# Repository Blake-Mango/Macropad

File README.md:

# Hyperion MacroPad
A macro pad built for multi platform use with a screen to show mode changes and display graphics. I’m going to try and make it wireless as well.

# PCB Assembly & Firmware

## Materials
You will need **all components listed in the Bill of Materials (BOM)** to assemble this board. + the 3d printed case.(currrently pretty bad) 

### Heres what the PCB should look like

---

## Assembly Steps

1. **Solder the KB2040**  
   Begin by attaching the KB2040 to the PCB.

2. **Solder all diodes**  
   Ensure *all diodes are facing the same direction* according to the silkscreen/polarity marking.

3. **Solder all switches**  
   Install and solder all mechanical switches.

4. **Solder remaining components**  
   Add the rest of the components from the BOM (connectors, headers, LEDs, etc.).

---

## Firmware

Firmware is provided in the **`hyperion`** file.  
It is a simple custom program created with help from ChatGPT.

To install:
1. Put the KB2040 into **UF2 bootloader mode**.  
2. Drag and drop the `hyperion` firmware file onto the device.  
3. The board will reboot automatically.

I have made a case but it is very bad i will be making a new case in a day or two just need to look around and see what looks good

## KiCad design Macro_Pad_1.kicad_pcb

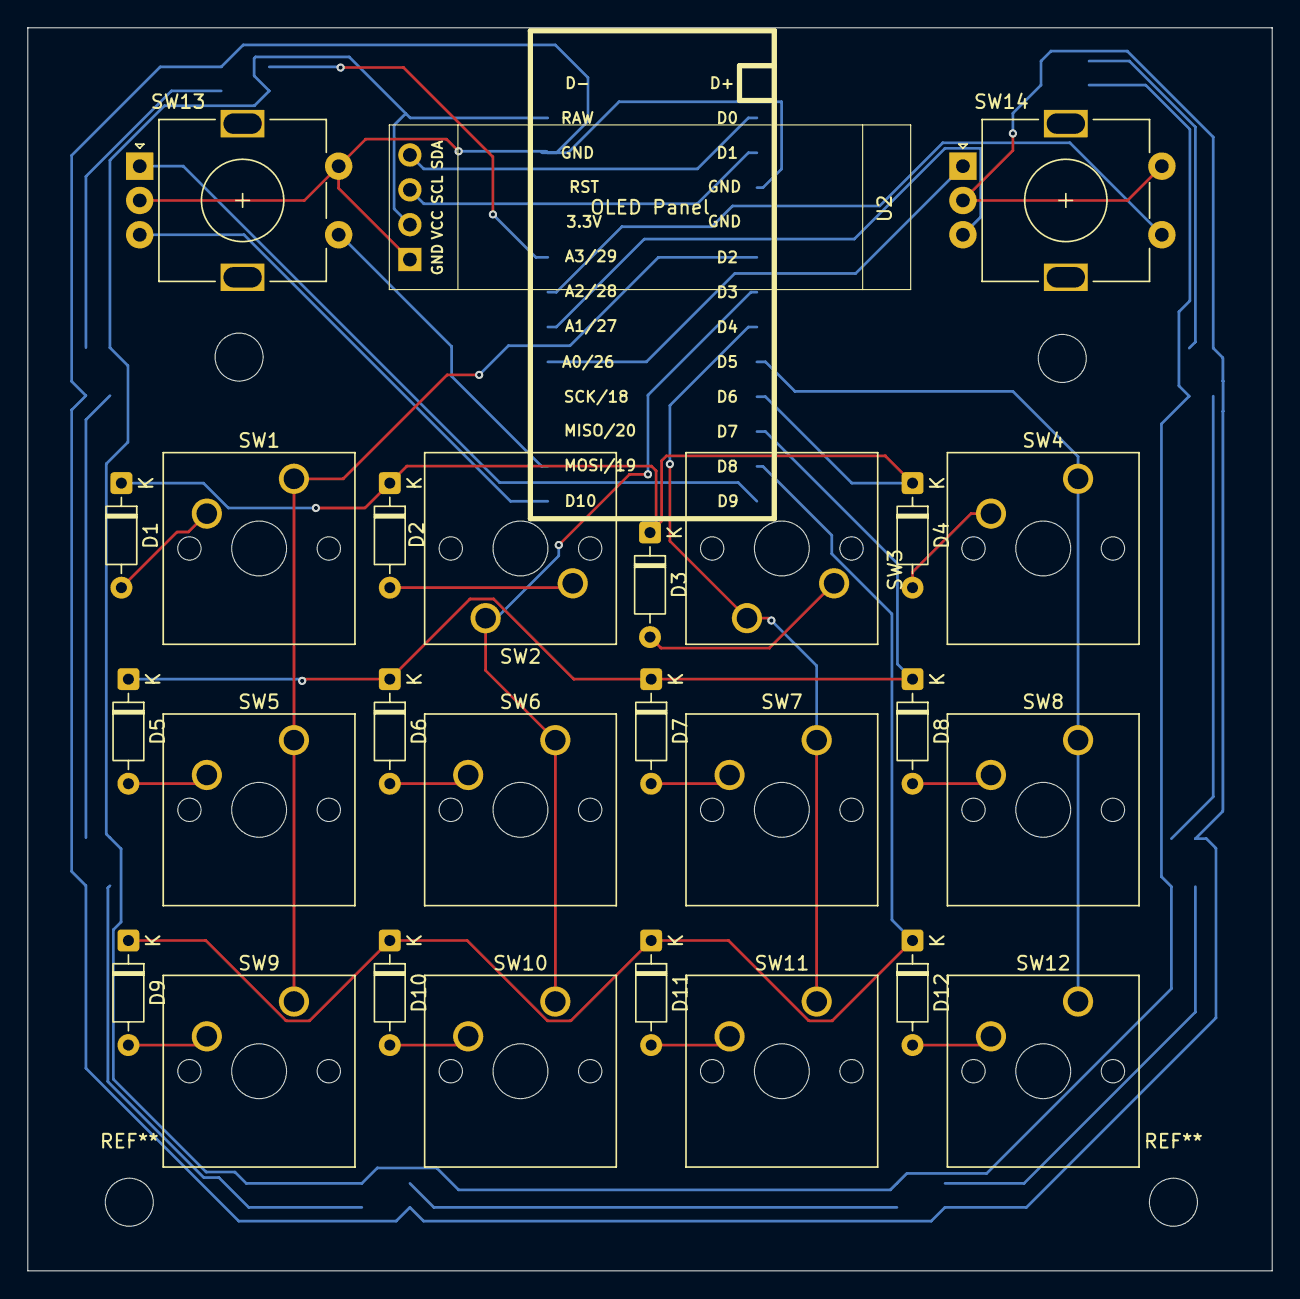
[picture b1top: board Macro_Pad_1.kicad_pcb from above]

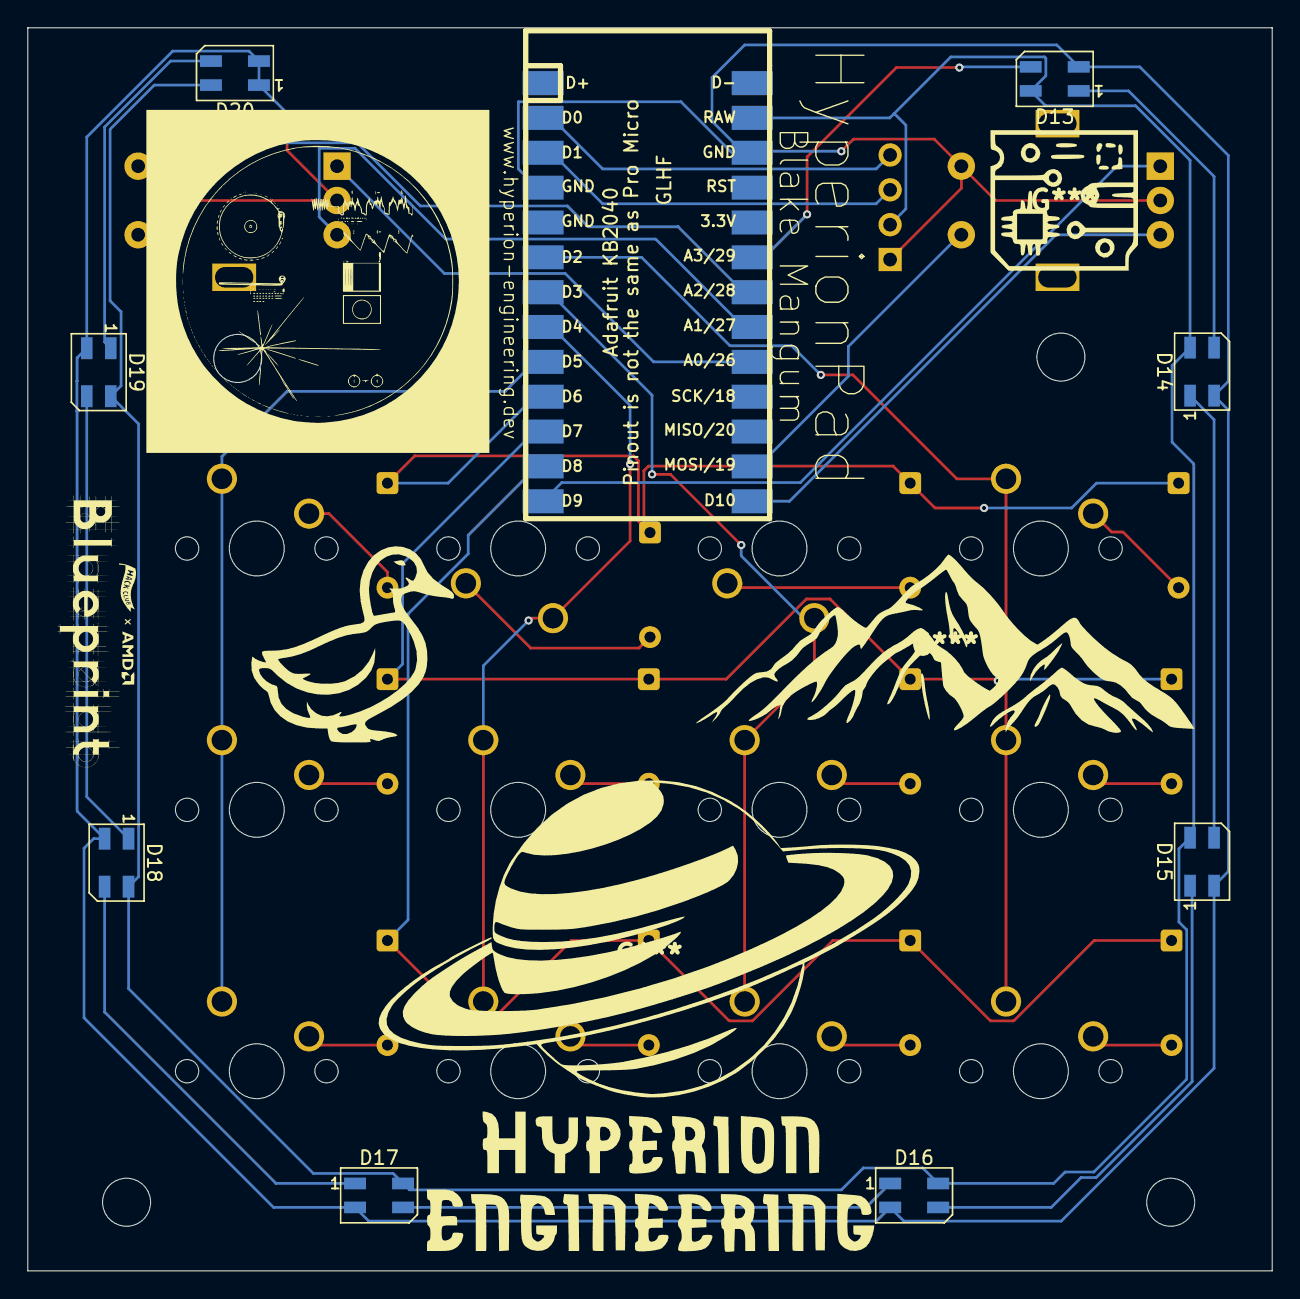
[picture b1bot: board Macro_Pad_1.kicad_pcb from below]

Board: 2 copper layers, 90.7 x 90.6 mm, 36 parts (9 on the bottom side), 37 nets.

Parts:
D1, D2, D3, D4, D5, D6, D7, D8, D9, D10, D11, D12: 1N4148; D_DO-35_SOD27_P7.62mm_Horizontal
D13, D14, D15, D16, D17, D18, D19, D20: SK6812MINI; LED_SK6812MINI_PLCC4_3.5x3.5mm_P1.75mm
SW1, SW2, SW3, SW4, SW5, SW6, SW7, SW8, SW9, SW10, SW11, SW12: SW_Push; SW_Cherry_MX_1.00u_PCB
SW13, SW14: RotaryEncoder_Switch; RotaryEncoder_Alps_EC11E-Switch_Vertical_H20mm
U1: kb2040
U2: 0.91 inch OLED; SSD1306-0.91-OLED-4pin-128x32

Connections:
A0/D26: SW14.A, U1.16 (GND)
A1/D27: SW14.B, U1.20 (A2/28)
A2/D28: SW14.S1, U1.19 (A3/29)
A3/D29: D13.3 (DIN), U1.18 (3.3v)
D0: U1.2 (D0), U2.4 (SDA)
D1: U1.3 (D1), U2.3 (SCL)
D2: SW1.1, SW5.1, SW9.1, U1.6 (D2)
D3: SW2.1, SW6.1, SW10.1, U1.7 (D3)
D4: SW3.1, SW7.1, SW11.1, U1.8 (D4)
D5: SW4.1, SW8.1, SW12.1, U1.9 (D5)
D6: D1.1 (K), D2.1 (K), D3.1 (K), D4.1 (K), U1.10 (D6)
D7: D5.1 (K), D6.1 (K), D7.1 (K), D8.1 (K), U1.11 (D7)
D8: D9.1 (K), D10.1 (K), D11.1 (K), D12.1 (K), U1.12 (D8)
D9: SW13.A, U1.13 (D9)
D10: SW13.B, U1.14 (D-)
GND: D13.2 (VSS), D14.2 (VSS), D15.2 (VSS), D16.2 (VSS), D17.2 (VSS), D18.2 (VSS), D19.2 (VSS), D20.1 (DOUT), D20.2 (VSS), SW13.C, SW13.S2, SW14.C, SW14.S2, U1.4 (GND), U1.15 (RAW), U2.1 (GND)
MOSI/D19: SW13.S1, U1.15 (RAW)
unnamed: D1.2 (A), SW1.2
unnamed: D2.2 (A), SW2.2
unnamed: D3.2 (A), SW3.2
unnamed: D4.2 (A), SW4.2
unnamed: D5.2 (A), SW5.2
unnamed: D6.2 (A), SW6.2
unnamed: D7.2 (A), SW7.2
unnamed: D8.2 (A), SW8.2
unnamed: D9.2 (A), SW9.2
unnamed: D10.2 (A), SW10.2
unnamed: D11.2 (A), SW11.2
unnamed: D12.2 (A), SW12.2
unnamed: D13.1 (DOUT), D14.3 (DIN)
unnamed: D14.1 (DOUT), D15.3 (DIN)
unnamed: D15.1 (DOUT), D16.3 (DIN)
unnamed: D16.1 (DOUT), D17.3 (DIN)
unnamed: D17.1 (DOUT), D18.3 (DIN)
unnamed: D18.1 (DOUT), D19.3 (DIN)
unnamed: D19.1 (DOUT), D20.3 (DIN)
PWR: D13.4 (VDD), D14.4 (VDD), D15.4 (VDD), D16.4 (VDD), D17.4 (VDD), D18.4 (VDD), D19.4 (VDD), D20.4 (VDD), U1.14 (D-), U2.2 (VCC)

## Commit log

2025-11-25 Enhance README with detailed assembly and firmware info
    Expanded README with assembly steps and firmware installation instructions.
2025-11-26 Revise case description for KB2040
    Updated the case information for the KB2040.
2025-11-29 Revise images and BOM note in README
    Updated the images and added a note about the 3D printed case.
